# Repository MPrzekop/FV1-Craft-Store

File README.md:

# Craft Store
#### FV-1 based multi-effect development platform that (almost) fits inside 1590b enclosure
Craft Store is a pedalboard friendly implementation of FV-1 with onboard USB programmer.

---

How it's different
---
On top of the default signal path:
- there's physical feedback loop going from right channel output to the left channel input 
- FV-1's left channel input can be blended into the pedal's output 

Controls:
---
- 0-2 FV-1 potentiometer inputs
- Volume
- mix - full dry to full wet
- clock - 4049 based variable sampling clock 42kHz down to super glitchy 2kHz
- feed - adds FV-1's left channel output to the output signal
- toggle - switches between built-in FV-1 programs and EEPROM
- 8 position program selector

Contents:
---
- [KiCad 8.0 project ](https://github.com/MPrzekop/FV1-Craft-Store/tree/main/Hardware/KiCad)
  - 2 effect boards and optional footswitch doughterboard

 - [3D printing files ](https://github.com/MPrzekop/FV1-Craft-Store/tree/main/Hardware/3DPrinting)
    - Case and lid, similar to 1590b just 2mm taller 
    - Knobs for 9mm potentiometers V6 is different from V5 that it has an inset to accommodate for 8 position switch thread collar. V5 variants to use depending on filament and printer.
 - [Spincad made example programs ](https://github.com/MPrzekop/FV1-Craft-Store/tree/main/Software)

Build Guide:
---
[BOM](https://github.com/MPrzekop/FV1-Craft-Store/blob/main/Hardware/KiCad/fv1.csv).

Most of the components are SMD so it may require some experience. I've tried to preserve both component ids and values on the PCB itself for ease of build and debugging.

Couple of tips:
- with normal 2.54 sockets and pins the boards may pivot on DC jack, I've soldered sockets when the board was lying on a flat surface to get the most clearance from the pins.
- Clock potentiometer is marked as 100K, this may be excessive as below 20kHz there's an audible hiss. I've tested with 20K and it was more controllable, but still glitchy (theoretically going down to 8kHz). If what you need is longer delays without much audio degradation I'd recommend putting 5K potentiometer there.
- The board stack is slightly too tall for a normal 1590b housing, to make the housing compatible you'll need to file down the lip on the lid, or add around 2mm spacing between the housing and the lid. 

Programming Guide:
---

On the board there's a **[ch341a](https://www.wch-ic.com/products/CH341.html)** programmer and **[24lc32](https://ww1.microchip.com/downloads/en/DeviceDoc/21072G.pdf)** EEPROM so any approaches for programming those are valid.
- you'll need drivers from the [ch341a vendor's page](https://www.wch-ic.com/products/CH341.html)
- follow [this tutorial](https://wiki.pedalpcb.com/wiki/Using_the_FV1Dev_on_Microsoft_Windows) for how to program the EEPROM

Creating programs:
---

[Best place to start](https://electric-canary.com/fv1start.html)

- The easiest way, by a mile, is to use [SpinCAD designer](https://github.com/HolyCityAudio/SpinCAD-Designer) 

- [SpinASM](https://spinsemi.com/products.html), FV-1 flavoured assembly

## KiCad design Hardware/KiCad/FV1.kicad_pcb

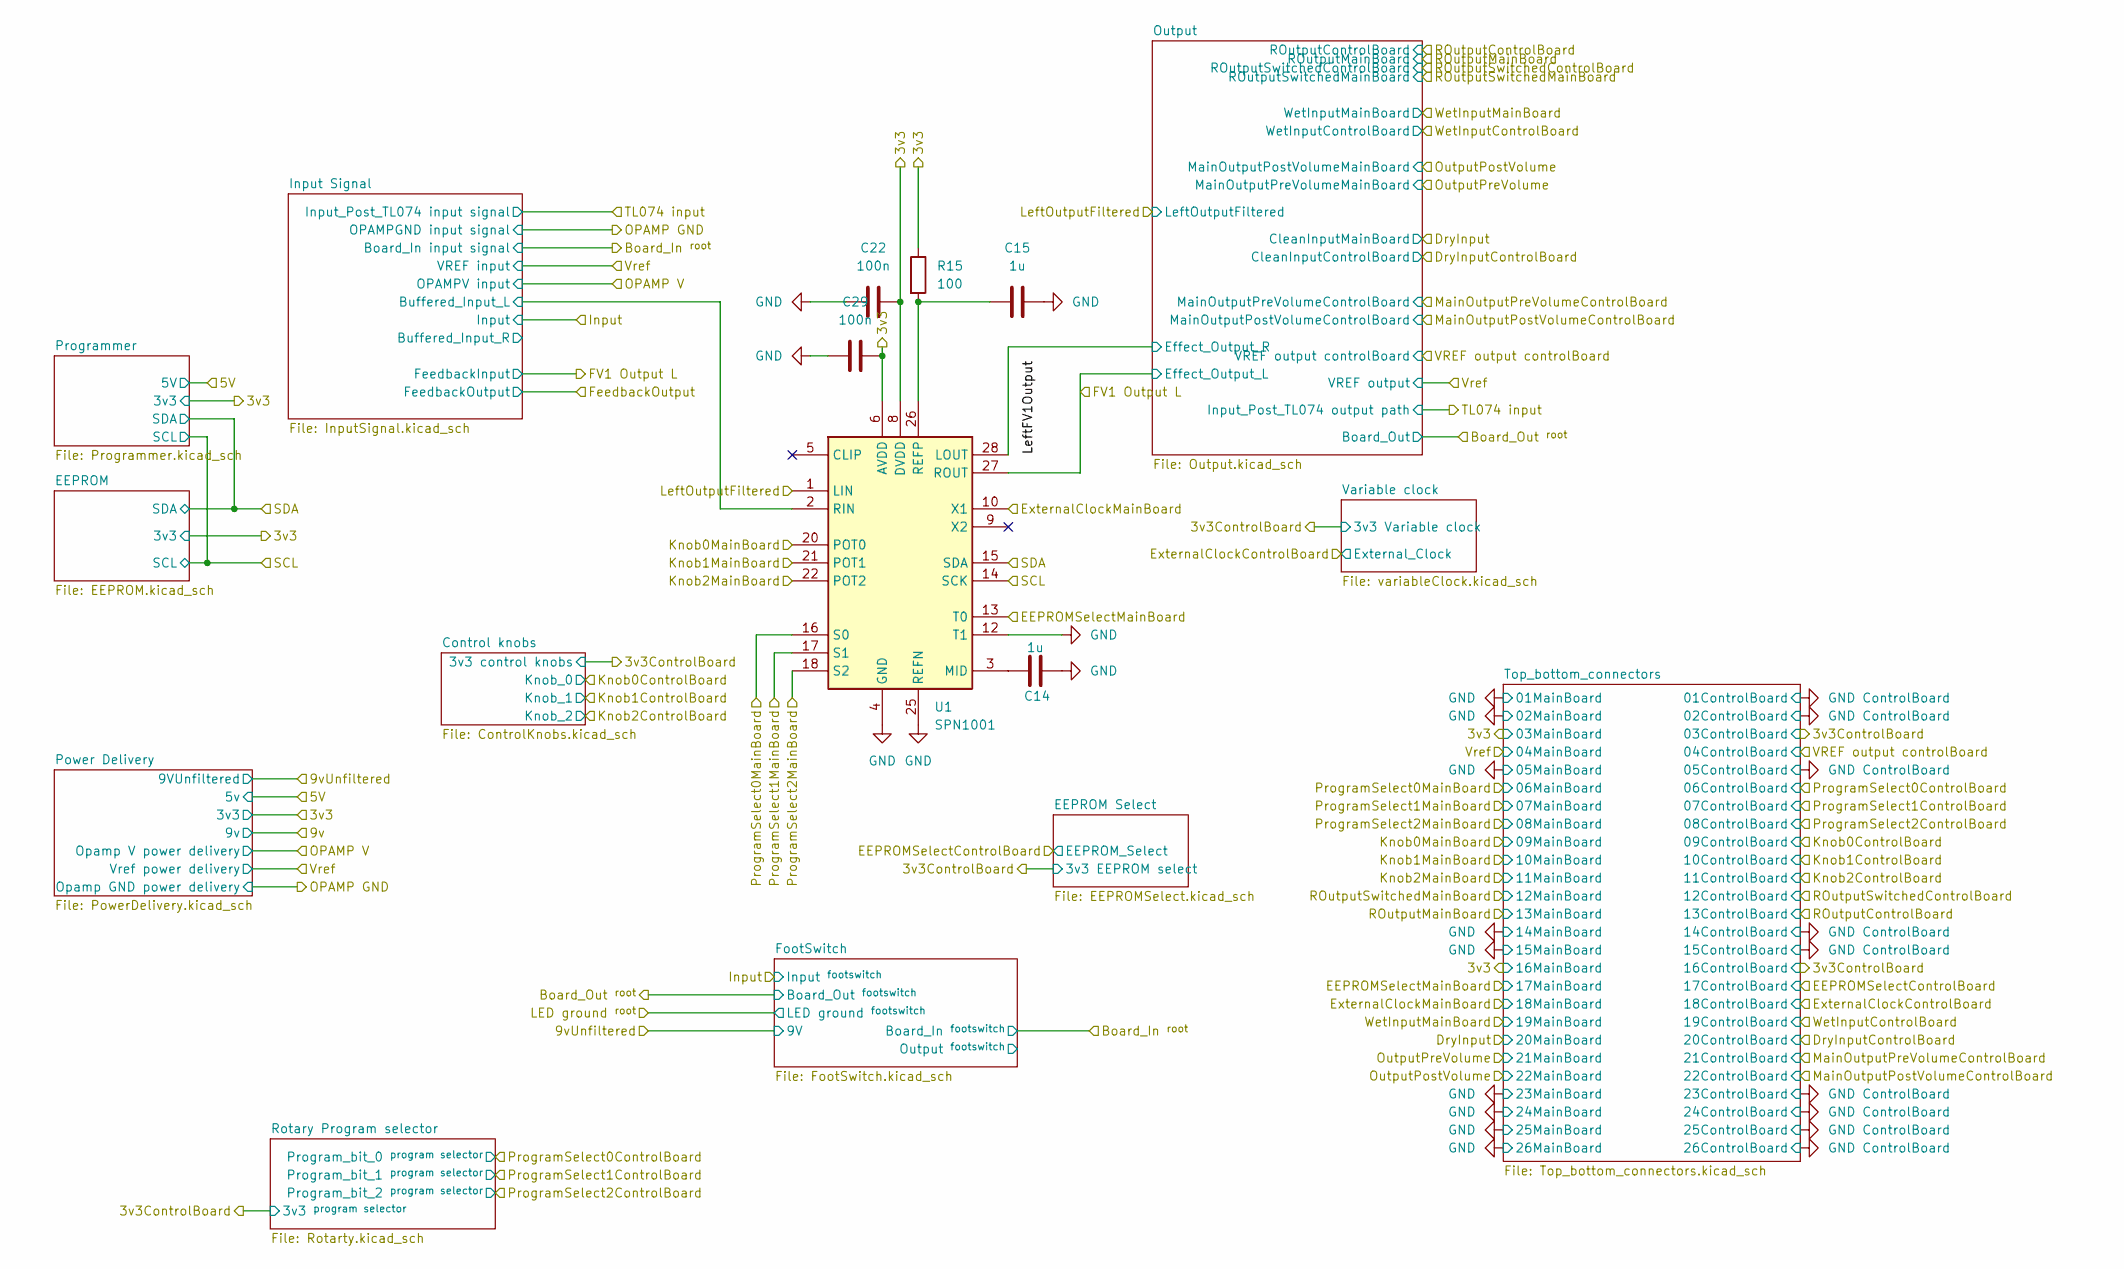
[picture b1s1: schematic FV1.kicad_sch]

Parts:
C14, C15: 1u; C_0603_1608Metric_Pad1.08x0.95mm_HandSolder
C22, C29: 100n; C_0603_1608Metric_Pad1.08x0.95mm_HandSolder
R15: 100; R_0603
U1: SPN1001; SOIC-28W_7.5x17.9mm_P1.27mm

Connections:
/3v3: C22.2, C29.2, R15.1, U1.6 (AVDD), U1.8 (DVDD), U1.23 (DVDD); also elsewhere on the board
/EEPROMSelectMainBoard: U1.13 (T0); also elsewhere on the board
/ExternalClockMainBoard: U1.10 (X1); also elsewhere on the board
/FV1 Output L: U1.27 (ROUT); also elsewhere on the board
/Input Signal/Buffered_Input_L: U1.2 (RIN); also elsewhere on the board
/Knob0MainBoard: U1.20 (POT0); also elsewhere on the board
/Knob1MainBoard: U1.21 (POT1); also elsewhere on the board
/Knob2MainBoard: U1.22 (POT2); also elsewhere on the board
/LeftOutputFiltered: U1.1 (LIN); also elsewhere on the board
/Output/Effect_Output_R: U1.28 (LOUT); also elsewhere on the board
/ProgramSelect0MainBoard: U1.16 (S0); also elsewhere on the board
/ProgramSelect1MainBoard: U1.17 (S1); also elsewhere on the board
/ProgramSelect2MainBoard: U1.18 (S2); also elsewhere on the board
/SCL: U1.14 (SCK); also elsewhere on the board
/SDA: U1.15 (SDA); also elsewhere on the board
GND: C14.1, C15.2, C22.1, C29.1, U1.4 (GND), U1.7 (GND), U1.11 (GND), U1.12 (T1), U1.19 (GND), U1.24 (GND), U1.25 (REFN); also elsewhere on the board
unnamed: C14.2, U1.3 (MID)
unnamed: C15.1, R15.2, U1.26 (REFP)

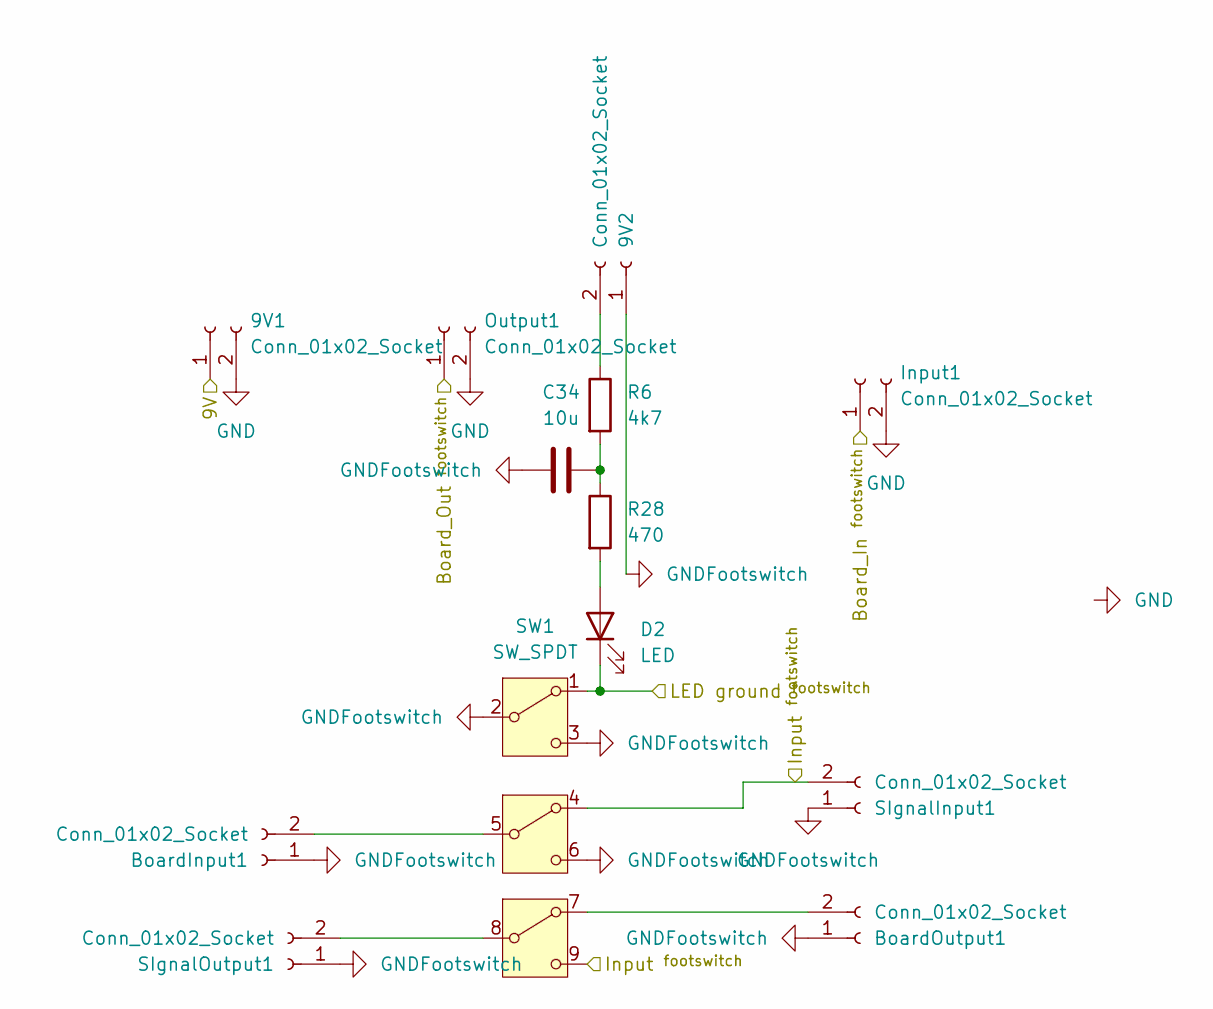
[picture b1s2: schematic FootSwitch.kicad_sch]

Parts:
9V1, 9V2: Conn_01x02_Socket; PinSocket_1x02_P2.54mm_Vertical
BoardInput1: Conn_01x02_Socket; PinSocket_1x02_P2.54mm_Vertical
BoardOutput1: Conn_01x02_Socket; PinSocket_1x02_P2.54mm_Vertical
C34: 10u; C_0603_1608Metric_Pad1.08x0.95mm_HandSolder
D2: LED; LED_D5.0mm
Input1: Conn_01x02_Socket; PinSocket_1x02_P2.54mm_Vertical
Output1: Conn_01x02_Socket; PinSocket_1x02_P2.54mm_Vertical
R6: 4k7; R_0603
R28: 470; R_0603
SIgnalInput1: Conn_01x02_Socket; PinSocket_1x02_P2.54mm_Vertical
SIgnalOutput1: Conn_01x02_Socket; PinSocket_1x02_P2.54mm_Vertical
SW1: SW_SPDT; 3PDT

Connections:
/9vUnfiltered: 9V1.1; also elsewhere on the board
/Board_Out ^{root}: Output1.1; also elsewhere on the board
/Input: SIgnalInput1.2, SW1.4 (A2), SW1.9 (C3)
/Input Signal/PrefilteredInput: Input1.1; also elsewhere on the board
/LED ground ^{root}: D2.1 (K), SW1.1 (A)
GND: 9V1.2, Input1.2, Output1.2; also elsewhere on the board
GNDFootswitch: 9V2.1, BoardInput1.1, BoardOutput1.1, C34.1, SIgnalInput1.1, SIgnalOutput1.1, SW1.2 (B), SW1.3 (C), SW1.6 (C2)
unnamed: 9V2.2, R6.1
unnamed: BoardInput1.2, SW1.5 (B2)
unnamed: BoardOutput1.2, SW1.7 (A3)
unnamed: C34.2, R6.2, R28.1
unnamed: D2.2 (A), R28.2
unnamed: SIgnalOutput1.2, SW1.8 (B3)

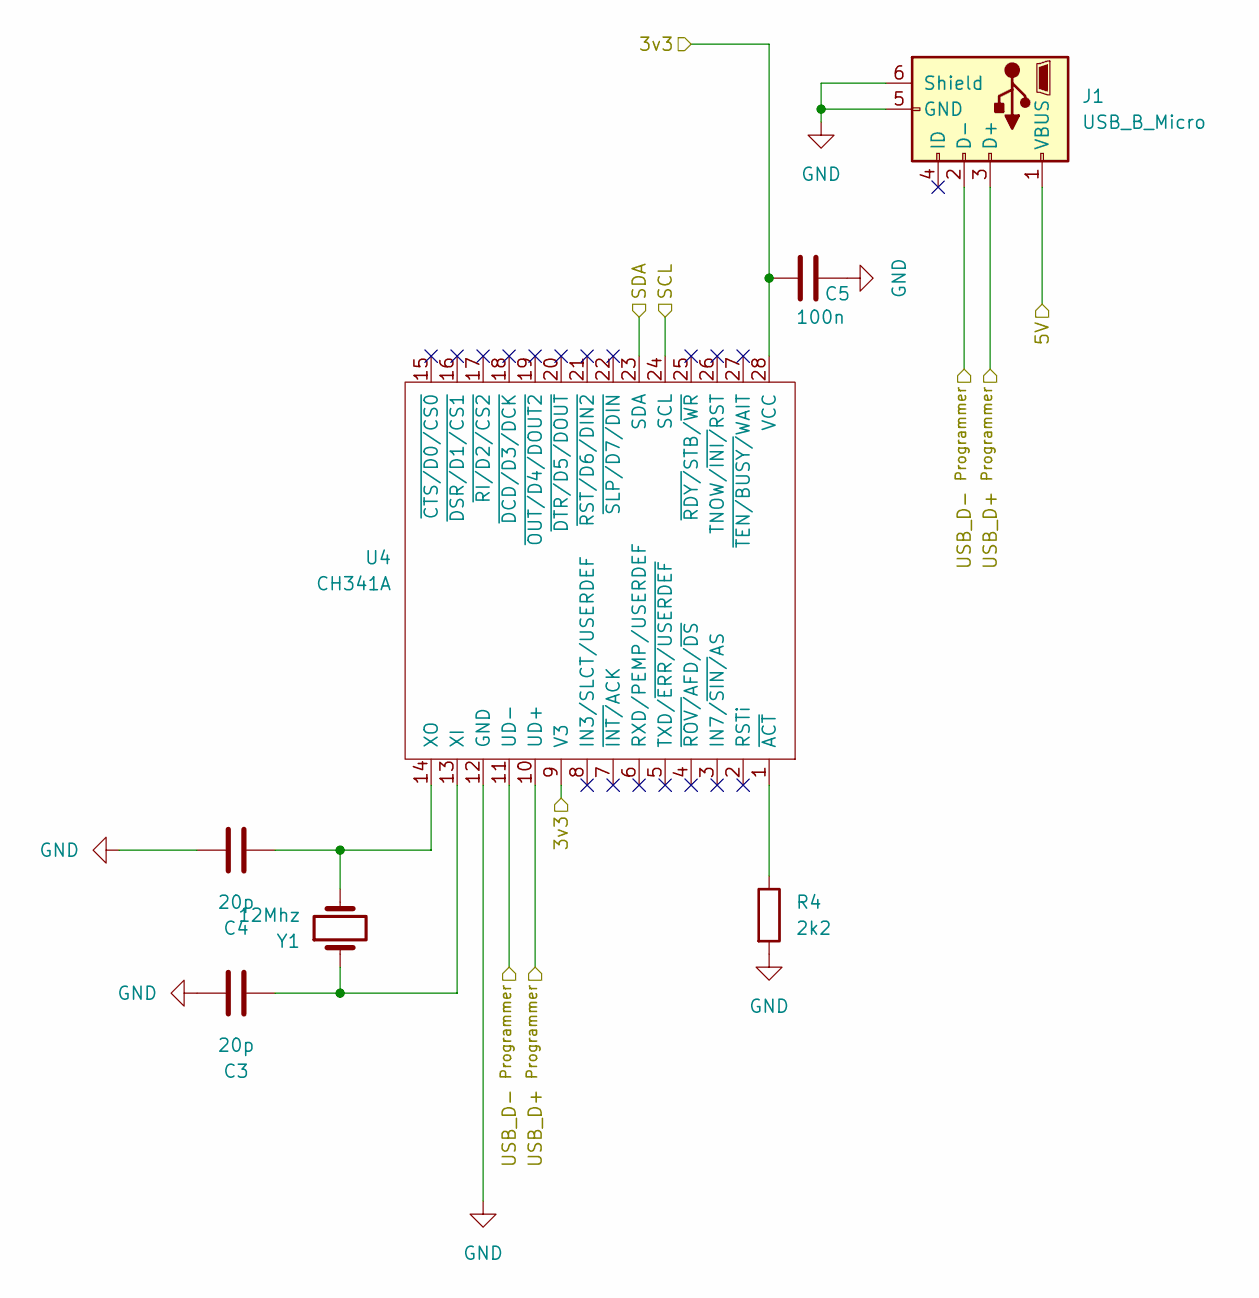
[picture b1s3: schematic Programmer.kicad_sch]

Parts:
C3, C4: 20p; C_0603_1608Metric_Pad1.08x0.95mm_HandSolder
C5: 100n; C_0603_1608Metric_Pad1.08x0.95mm_HandSolder
J1: USB_B_Micro; USB_Micro-AB_Molex_47590-0001
R4: 2k2; R_0603
U4: CH341A; SOIC-28W_7.5x18.7mm_P1.27mm
Y1: 12Mhz; Crystal_HC49-4H_Vertical

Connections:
/3v3: C5.1, U4.9 (V3), U4.28 (VCC); also elsewhere on the board
/5V: J1.1 (VBUS); also elsewhere on the board
/Programmer/USB_D+ ^{Programmer}: J1.3 (D+), U4.10 (UD+)
/Programmer/USB_D- ^{Programmer}: J1.2 (D-), U4.11 (UD-)
/SCL: U4.24 (SCL); also elsewhere on the board
/SDA: U4.23 (SDA); also elsewhere on the board
GND: C3.2, C4.2, C5.2, J1.5 (GND), J1.6 (Shield), R4.2, U4.12 (GND); also elsewhere on the board
unnamed: C3.1, U4.13 (XI), Y1.1
unnamed: C4.1, U4.14 (XO), Y1.2
unnamed: R4.1, U4.1 (~ACT)

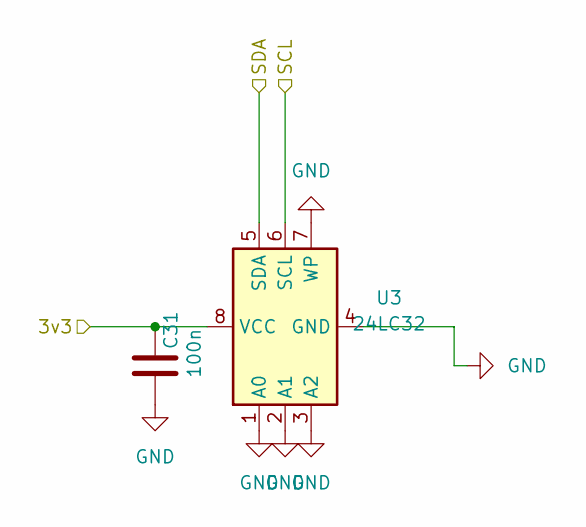
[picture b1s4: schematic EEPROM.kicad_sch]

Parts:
C31: 100n; C_0603_1608Metric_Pad1.08x0.95mm_HandSolder
U3: 24LC32; DIP-8_W7.62mm_Socket

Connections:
/3v3: C31.2, U3.8 (VCC); also elsewhere on the board
/SCL: U3.6 (SCL); also elsewhere on the board
/SDA: U3.5 (SDA); also elsewhere on the board
GND: C31.1, U3.1 (A0), U3.2 (A1), U3.3 (A2), U3.4 (GND), U3.7 (WP); also elsewhere on the board

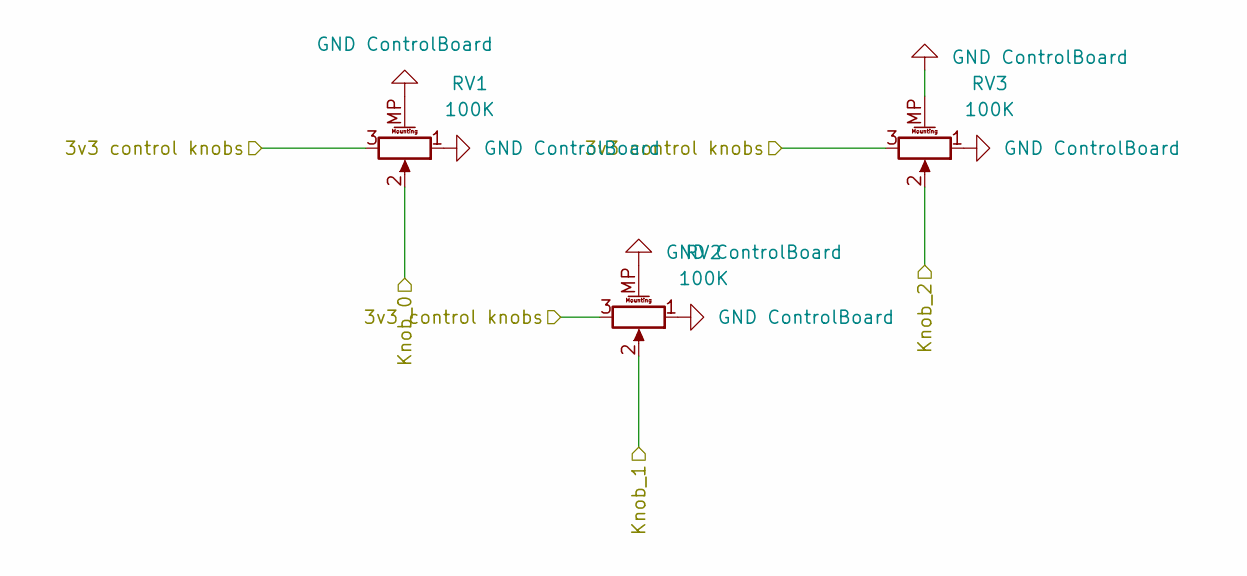
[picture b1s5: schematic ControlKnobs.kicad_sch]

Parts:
RV1, RV2, RV3: 100K; Pot_9mm_Knurl_NoDet

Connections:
/EEPROM Select/3v3: RV1.3, RV2.3, RV3.3; also elsewhere on the board
/Knob0ControlBoard: RV1.2; also elsewhere on the board
/Knob1ControlBoard: RV2.2; also elsewhere on the board
/Knob2ControlBoard: RV3.2; also elsewhere on the board
GND ControlBoard: RV1.1, RV1.MP (MountPin), RV2.1, RV2.MP (MountPin), RV3.1, RV3.MP (MountPin); also elsewhere on the board

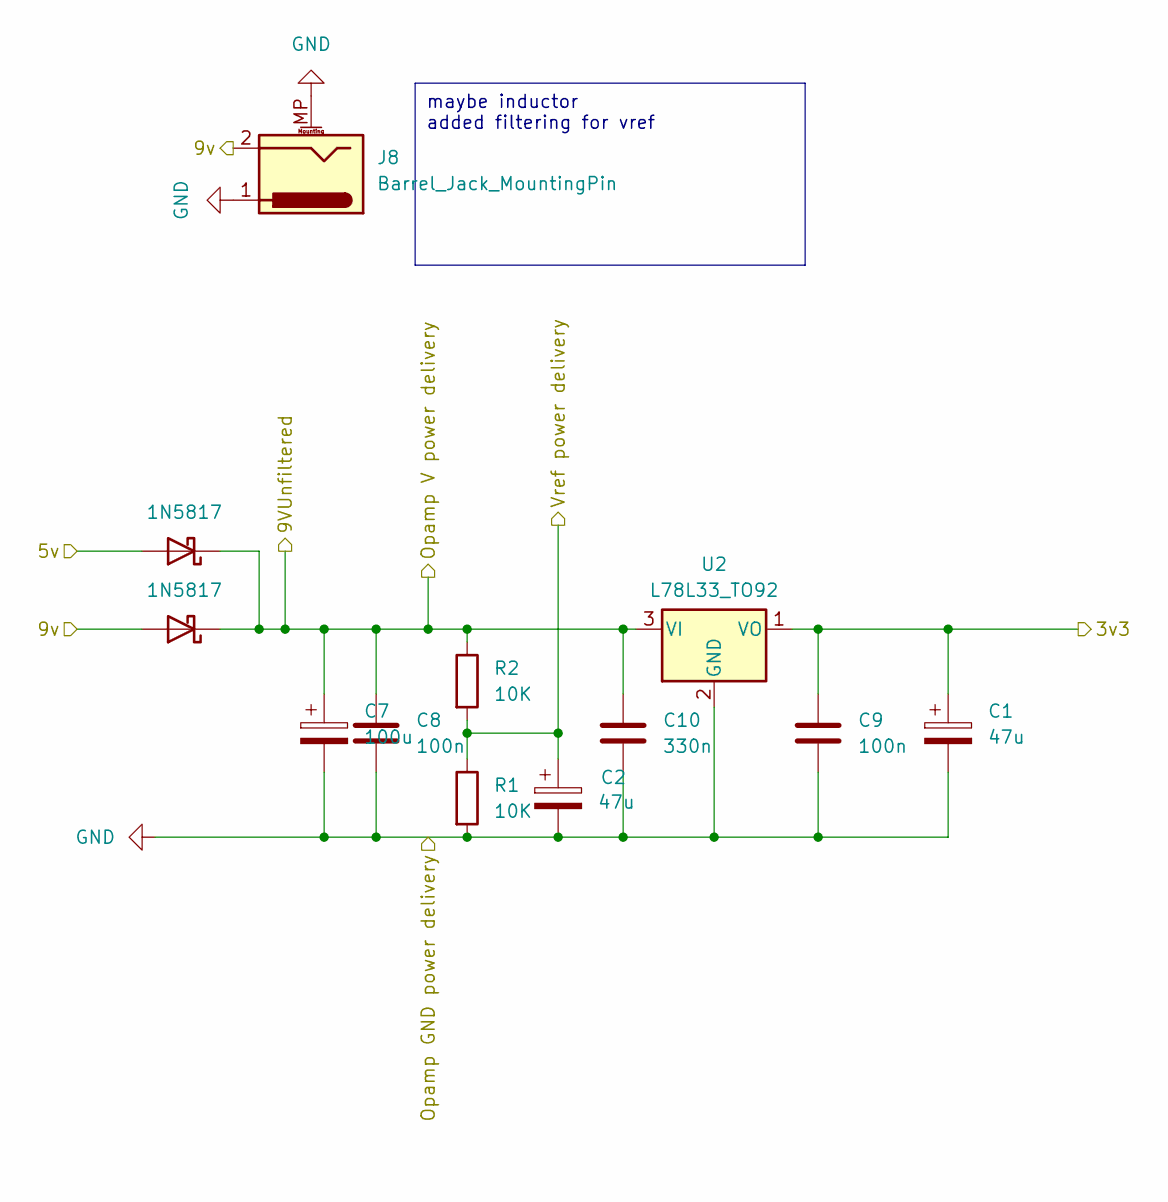
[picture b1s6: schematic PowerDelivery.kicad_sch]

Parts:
C1, C2: 47u; CP_Elec_5x5.4
C7: 100u; CP_Elec_6.3x5.4
C8, C9: 100n; C_0603_1608Metric_Pad1.08x0.95mm_HandSolder
C10: 330n; C_0603_1608Metric_Pad1.08x0.95mm_HandSolder
D1, D12: 1N5817; D_DO-41_SOD81_P10.16mm_Horizontal
J8: Barrel_Jack_MountingPin; BarrelJack_Horizontal
R1, R2: 10K; R_0603
U2: L78L33_TO92; TO-92_Inline

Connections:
/3v3: C1.1, C9.1, U2.1 (VO); also elsewhere on the board
/5V: D12.2 (A); also elsewhere on the board
/9v: D1.2 (A), J8.2
/9vUnfiltered: C7.1, C8.1, C10.1, D1.1 (K), D12.1 (K), R2.1, U2.3 (VI); also elsewhere on the board
/Vref: C2.1, R1.1, R2.2; also elsewhere on the board
GND: C1.2, C2.2, C7.2, C8.2, C9.2, C10.2, J8.1, J8.MP (MountPin), R1.2, U2.2 (GND); also elsewhere on the board

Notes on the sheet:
maybe inductor added filtering for vref

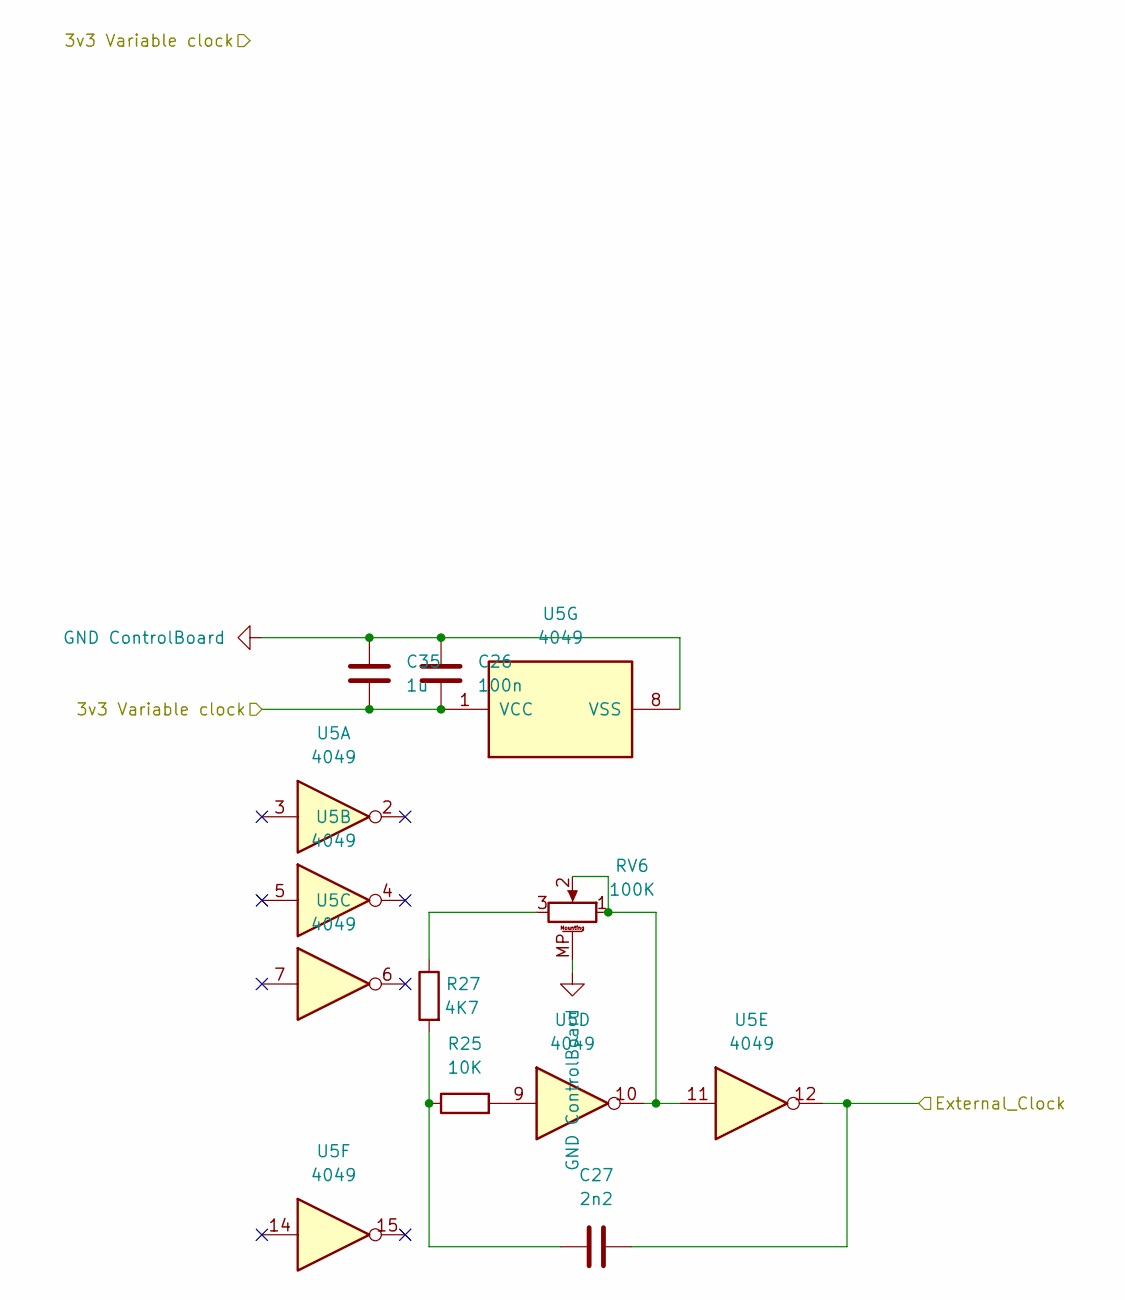
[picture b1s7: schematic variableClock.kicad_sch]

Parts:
C26: 100n; C_0603_1608Metric_Pad1.08x0.95mm_HandSolder
C27: 2n2; C_0603_1608Metric_Pad1.08x0.95mm_HandSolder
C35: 1u; C_0603_1608Metric_Pad1.08x0.95mm_HandSolder
R25: 10K; R_0603
R27: 4K7; R_0603
RV6: 100K; Pot_9mm_Knurl_NoDet
U5: 4049; CERDIP-16_W7.62mm_SideBrazed

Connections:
/EEPROM Select/3v3: C26.2, C35.2, U5.1 (VCC); also elsewhere on the board
/ExternalClockControlBoard: C27.2, U5.12; also elsewhere on the board
GND ControlBoard: C26.1, C35.1, RV6.MP (MountPin), U5.8 (VSS); also elsewhere on the board
unnamed: C27.1, R25.1, R27.2
unnamed: R25.2, U5.9
unnamed: R27.1, RV6.3
unnamed: RV6.1, RV6.2, U5.10, U5.11

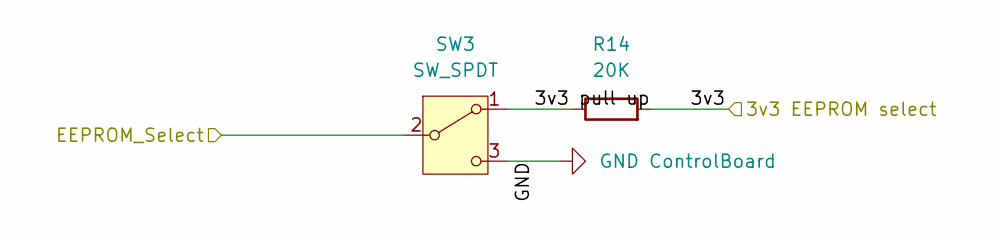
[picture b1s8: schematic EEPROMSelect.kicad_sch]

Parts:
R14: 20K; R_0603
SW3: SW_SPDT; SW_Toggle_Blue_wSlots

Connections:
/EEPROM Select/3v3: R14.2; also elsewhere on the board
/EEPROMSelectControlBoard: SW3.2 (B); also elsewhere on the board
GND ControlBoard: SW3.3 (C); also elsewhere on the board
unnamed: R14.1, SW3.1 (A)

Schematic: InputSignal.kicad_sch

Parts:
C6, C11, C36: 100n; C_0603_1608Metric_Pad1.08x0.95mm_HandSolder
C12: 1u; C_0603_1608Metric_Pad1.08x0.95mm_HandSolder
C13: 1n; C_0603_1608Metric_Pad1.08x0.95mm_HandSolder
R10, R13: 1K; R_0603
R11, R12: 1M; R_0603
U6: TL074; DIP-14_W7.62mm_Socket

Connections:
/9vUnfiltered: C6.1, U6.4 (V+); also elsewhere on the board
/Input Signal/Buffered_Input_L: C13.2, R13.2; also elsewhere on the board
/Input Signal/FilteredInput: R10.2, R12.1, U6.5 (+)
/Input Signal/PrefilteredInput: C11.1, R11.2; also elsewhere on the board
/TL074 input: C12.1, U6.6 (-), U6.7; also elsewhere on the board
/Vref: C36.2, R12.2; also elsewhere on the board
GND: C6.2, C13.1, C36.1, R11.1, U6.11 (V-); also elsewhere on the board
unnamed: C11.2, R10.1
unnamed: C12.2, R13.1

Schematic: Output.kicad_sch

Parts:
C16, C17, C18, C21, C24, C30: 1u; C_0603_1608Metric_Pad1.08x0.95mm_HandSolder
C19: 220p; C_0603_1608Metric_Pad1.08x0.95mm_HandSolder
C20, C28: 470p; C_0603_1608Metric_Pad1.08x0.95mm_HandSolder
C23, C25: 2n2; C_0603_1608Metric_Pad1.08x0.95mm_HandSolder
C32: 1n; C_0603_1608Metric_Pad1.08x0.95mm_HandSolder
C37, C38: 100n; C_0603_1608Metric_Pad1.08x0.95mm_HandSolder
R3, R16, R26: 1K; R_0603
R5, R17, R18, R19, R20, R21, R22, R30, R31: 15K; R_0603
R23: 100; R_0603
R24: 100K; R_0603
RV4: 100K; Pot_9mm_Knurl_NoDet
RV5, RV7: B10K; Pot_9mm_Knurl_NoDet
U6: TL074; DIP-14_W7.62mm_Socket

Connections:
/Board_Out ^{root}: C21.2, R24.2; also elsewhere on the board
/DryInputControlBoard: RV5.3; also elsewhere on the board
/FV1 Output L: C16.1, C30.1; also elsewhere on the board
/LeftOutputFiltered: C32.2, R3.2; also elsewhere on the board
/MainOutputPostVolumeControlBoard: C19.2, RV4.2, RV4.3; also elsewhere on the board
/MainOutputPreVolumeControlBoard: C19.1, RV4.1; also elsewhere on the board
/Output/DryInput: R18.2, R19.1; also elsewhere on the board
/Output/Effect_Output_R: C24.1; also elsewhere on the board
/Output/MixedBufferedOutput: R23.1, U6.1; also elsewhere on the board
/Output/MixedPrebufferedOutput: R19.2, R20.2, U6.2 (-); also elsewhere on the board
/ROutputControlBoard: RV7.3; also elsewhere on the board
/ROutputMainBoard: C25.2, R26.2; also elsewhere on the board
/ROutputSwitchedControlBoard: R5.2; also elsewhere on the board
/ROutputSwitchedMainBoard: C28.1, R30.1, R31.2, U6.13 (-); also elsewhere on the board
/TL074 input: R21.2; also elsewhere on the board
/VREF output controlBoard: C38.1, RV5.2, RV7.1; also elsewhere on the board
/Vref: C37.2, U6.3 (+), U6.10 (+), U6.12 (+); also elsewhere on the board
/WetInputControlBoard: RV5.1; also elsewhere on the board
/WetInputMainBoard: R17.2, R20.1; also elsewhere on the board
GND: C23.1, C25.1, C32.1, C37.1, R24.1; also elsewhere on the board
GND ControlBoard: C38.2, RV4.MP (MountPin), RV5.MP (MountPin), RV7.MP (MountPin); also elsewhere on the board
unnamed: C16.2, R16.1
unnamed: C17.1, C28.2, R31.1, U6.14
unnamed: C17.2, R17.1
unnamed: C18.1, C20.2, R22.2, U6.8
unnamed: C18.2, R18.1
unnamed: C21.1, R23.2
unnamed: C23.2, R16.2, R30.2
unnamed: C24.2, R26.1
unnamed: C30.2, R3.1
unnamed: R5.1, RV7.2
unnamed: C20.1, R21.1, R22.1, U6.9 (-)

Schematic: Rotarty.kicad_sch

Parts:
D3, D4, D5, D6, D7, D8, D9, D10, D11: 1N914; D_SOD-323_HandSoldering
R7, R8, R9: 100K; R_0603
SW2: SW_Rotary_1x8_MP; SR16

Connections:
/EEPROM Select/3v3: SW2.9; also elsewhere on the board
/ProgramSelect0ControlBoard: D3.1 (K), D5.1 (K), D9.1 (K), R7.1, SW2.2; also elsewhere on the board
/ProgramSelect1ControlBoard: D4.1 (K), D7.1 (K), D10.1 (K), R8.1, SW2.3; also elsewhere on the board
/ProgramSelect2ControlBoard: D6.1 (K), D8.1 (K), D11.1 (K), R9.1, SW2.5; also elsewhere on the board
GND ControlBoard: R7.2, R8.2, R9.2; also elsewhere on the board
unnamed: D3.2 (A), D4.2 (A), SW2.4
unnamed: D5.2 (A), D6.2 (A), SW2.6
unnamed: D7.2 (A), D8.2 (A), SW2.7
unnamed: D9.2 (A), D10.2 (A), D11.2 (A), SW2.8

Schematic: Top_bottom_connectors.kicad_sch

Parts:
J4, J5, J6: Conn_01x13; PinSocket_1x13_P2.54mm_Vertical
J7: Conn_01x13; PinHeader_1x13_P2.54mm_Vertical

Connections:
/3v3: J4.3, J5.3; also elsewhere on the board
/DryInputControlBoard: J7.7; also elsewhere on the board
/EEPROM Select/3v3: J6.3, J7.3; also elsewhere on the board
/EEPROMSelectControlBoard: J7.4; also elsewhere on the board
/EEPROMSelectMainBoard: J5.4; also elsewhere on the board
/ExternalClockControlBoard: J7.5; also elsewhere on the board
/ExternalClockMainBoard: J5.5; also elsewhere on the board
/Knob0ControlBoard: J6.9; also elsewhere on the board
/Knob0MainBoard: J4.9; also elsewhere on the board
/Knob1ControlBoard: J6.10; also elsewhere on the board
/Knob1MainBoard: J4.10; also elsewhere on the board
/Knob2ControlBoard: J6.11; also elsewhere on the board
/Knob2MainBoard: J4.11; also elsewhere on the board
/MainOutputPostVolumeControlBoard: J7.9; also elsewhere on the board
/MainOutputPreVolumeControlBoard: J7.8; also elsewhere on the board
/Output/DryInput: J5.7; also elsewhere on the board
/Output/MixedBufferedOutput: J5.9; also elsewhere on the board
/Output/MixedPrebufferedOutput: J5.8; also elsewhere on the board
/ProgramSelect0ControlBoard: J6.6; also elsewhere on the board
/ProgramSelect0MainBoard: J4.6; also elsewhere on the board
/ProgramSelect1ControlBoard: J6.7; also elsewhere on the board
/ProgramSelect1MainBoard: J4.7; also elsewhere on the board
/ProgramSelect2ControlBoard: J6.8; also elsewhere on the board
/ProgramSelect2MainBoard: J4.8; also elsewhere on the board
/ROutputControlBoard: J6.13; also elsewhere on the board
/ROutputMainBoard: J4.13; also elsewhere on the board
/ROutputSwitchedControlBoard: J6.12; also elsewhere on the board
/ROutputSwitchedMainBoard: J4.12; also elsewhere on the board
/VREF output controlBoard: J6.4; also elsewhere on the board
/Vref: J4.4; also elsewhere on the board
/WetInputControlBoard: J7.6; also elsewhere on the board
/WetInputMainBoard: J5.6; also elsewhere on the board
GND: J4.1, J4.2, J4.5, J5.1, J5.2, J5.10, J5.11, J5.12, J5.13; also elsewhere on the board
GND ControlBoard: J6.1, J6.2, J6.5, J7.1, J7.2, J7.10, J7.11, J7.12, J7.13; also elsewhere on the board

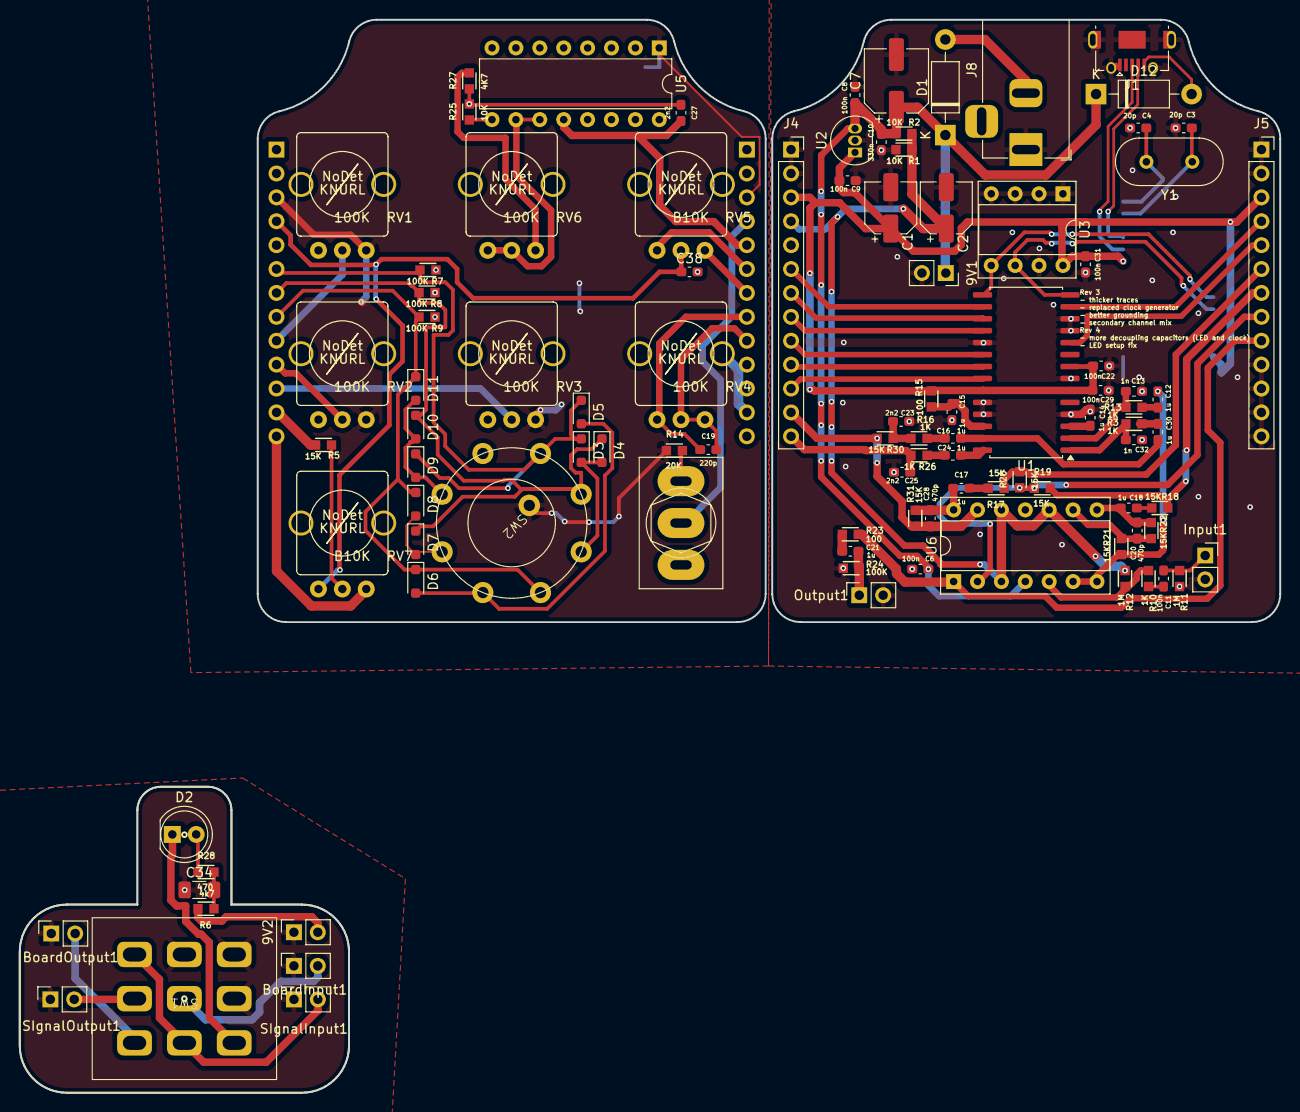
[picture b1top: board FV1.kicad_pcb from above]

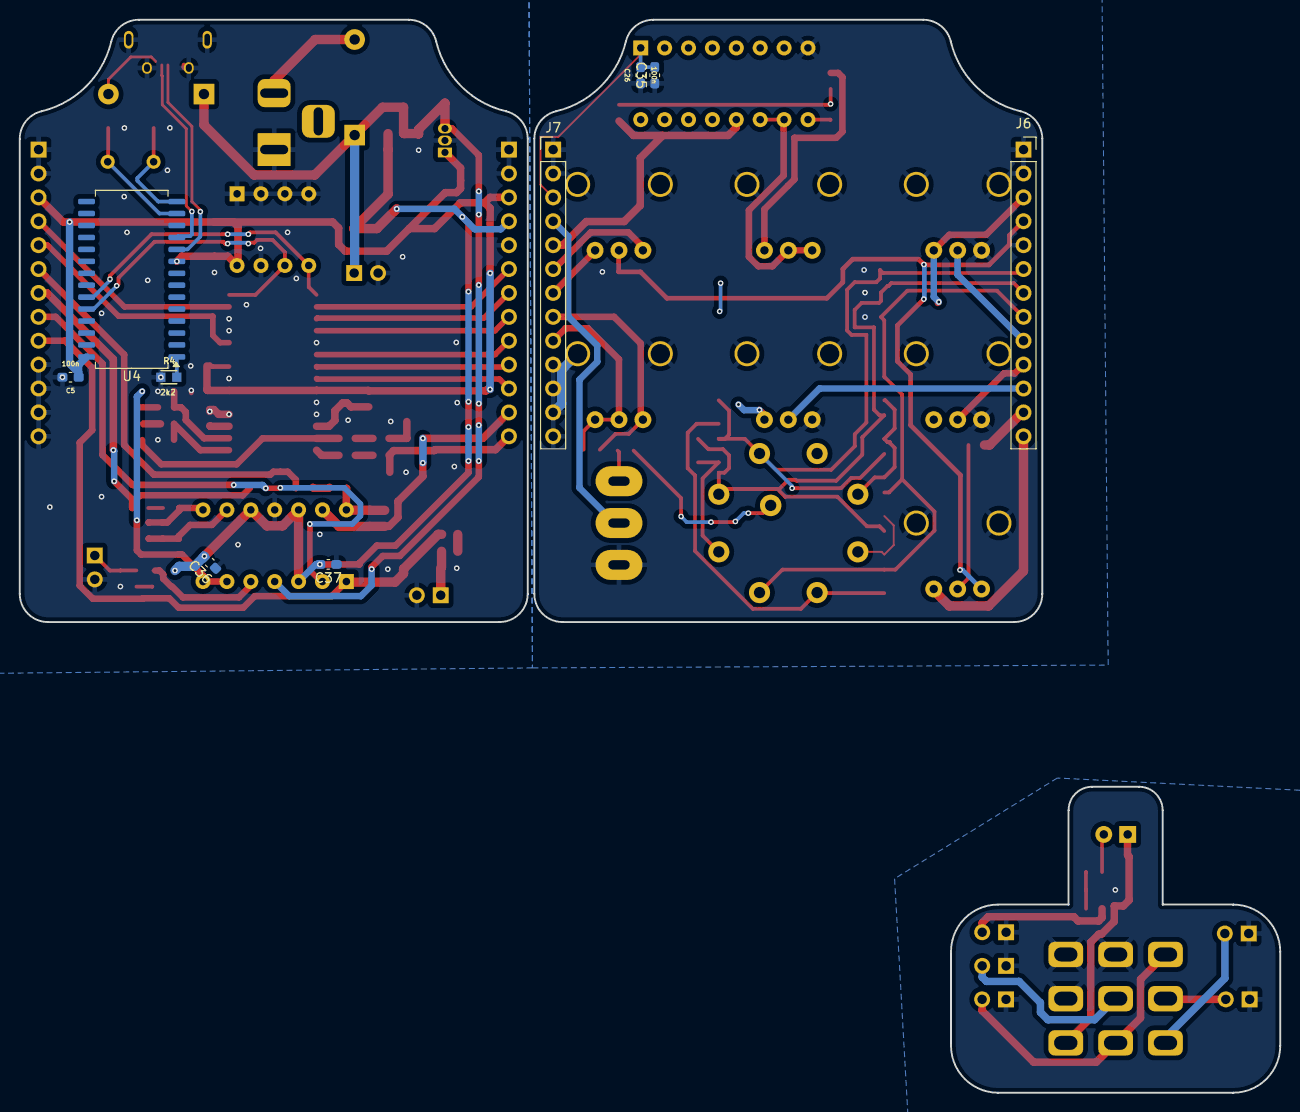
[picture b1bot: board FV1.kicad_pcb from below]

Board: 2 copper layers, 134.0 x 114.1 mm, 110 parts (9 on the bottom side), 85 nets.

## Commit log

2025-02-01 removed backup
